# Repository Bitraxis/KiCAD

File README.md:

# My repo for KiCad projects we do at school

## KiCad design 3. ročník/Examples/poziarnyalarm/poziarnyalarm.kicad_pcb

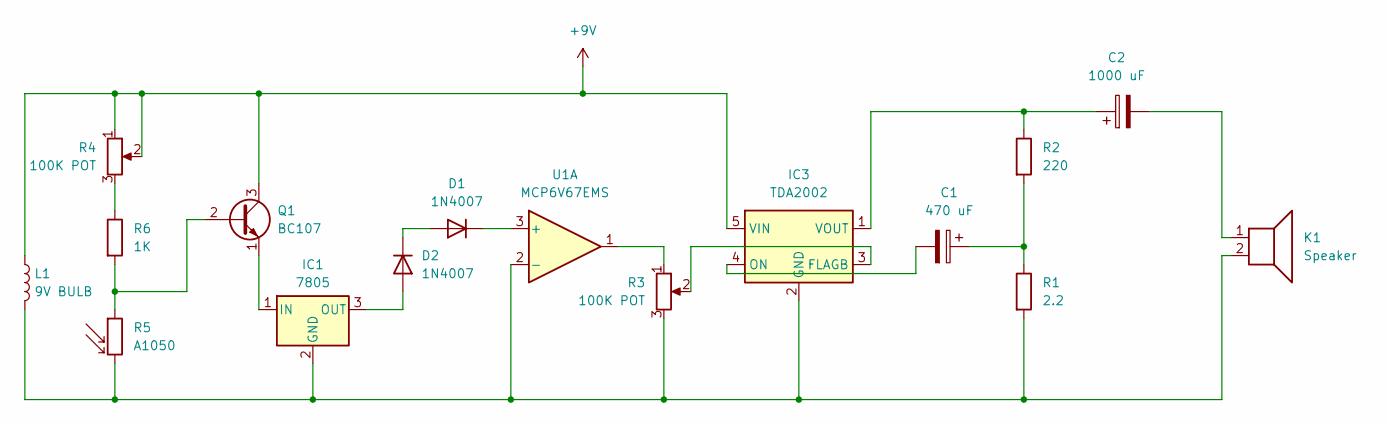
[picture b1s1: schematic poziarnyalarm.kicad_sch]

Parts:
C1: 470 uF; CP_Radial_D5.0mm_P2.50mm
C2: 1000 uF; CP_Radial_D5.0mm_P2.50mm
D1, D2: 1N4007; D_DO-35_SOD27_P10.16mm_Horizontal
IC1: 7805; TO-220F-3_Vertical
IC3: TDA2002; SOT-353_SC-70-5
K1: Speaker; Speaker_CUI_CMR-1206S-67
L1: 9V BULB; L_Radial_D7.0mm_P3.00mm
Q1: BC107; TO-18-3
R1: 2.2; R_Axial_DIN0207_L6.3mm_D2.5mm_P7.62mm_Horizontal
R2: 220; R_Axial_DIN0207_L6.3mm_D2.5mm_P7.62mm_Horizontal
R3, R4: 100K POT; Potentiometer_ACP_CA6-H2,5_Horizontal
R5: A1050; R_LDR_D6.4mm_P3.4mm_Vertical
R6: 1K; R_Axial_DIN0207_L6.3mm_D2.5mm_P7.62mm_Horizontal
U1: MCP6V67EMS; R_Array_BUS_SIP8

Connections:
+9V: IC3.5 (VIN), L1.1, Q1.3 (C), R4.1, R4.2
unnamed: C1.1, R1.1, R2.2
unnamed: C2.2, K1.1
unnamed: D1.2 (A), D2.1 (K)
unnamed: D1.1 (K), U1.3 (+)
unnamed: D2.2 (A), IC1.3 (OUT)
unnamed: IC1.2 (GND), IC3.2 (GND), K1.2, L1.2, R1.2, R3.3, R5.2, U1.2 (-)
unnamed: IC1.1 (IN), Q1.1 (E)
unnamed: IC3.3 (FLAGB), R3.2
unnamed: C1.2, IC3.4 (ON)
unnamed: C2.1, IC3.1 (VOUT), R2.1
unnamed: Q1.2 (B), R5.1, R6.2
unnamed: R3.1, U1.1
unnamed: R4.3, R6.1

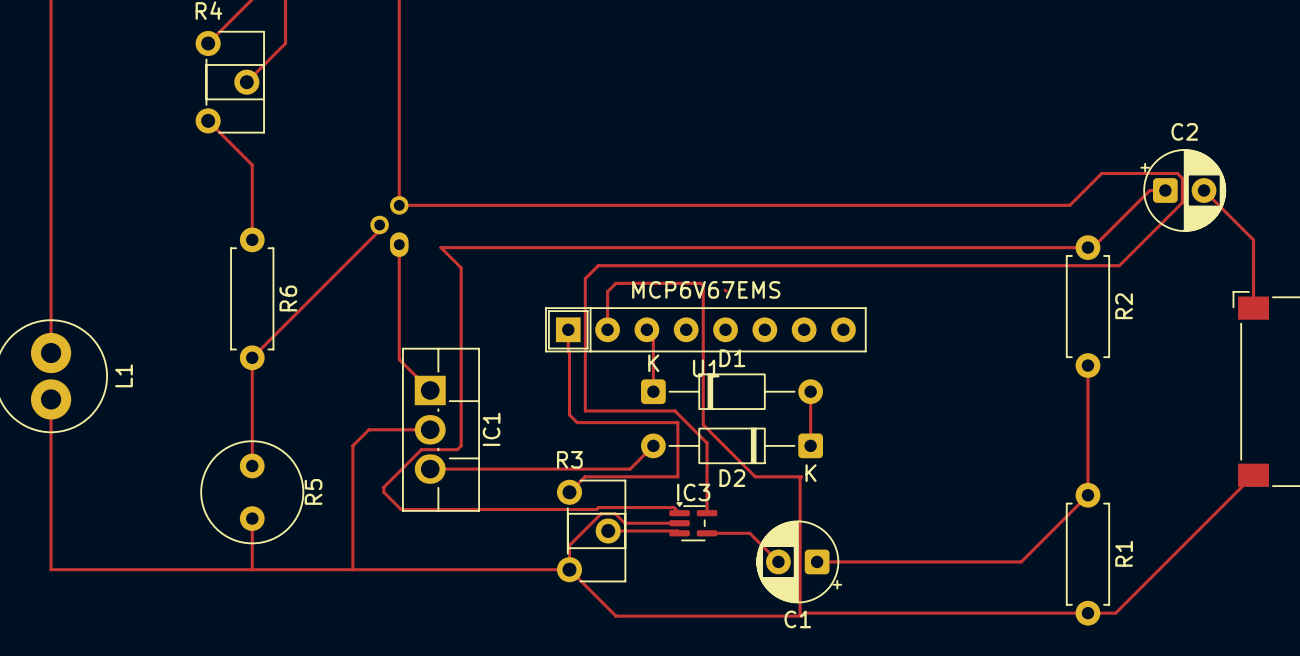
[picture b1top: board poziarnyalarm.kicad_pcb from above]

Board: 2 copper layers, 16 parts (1 on the bottom side), 14 nets.

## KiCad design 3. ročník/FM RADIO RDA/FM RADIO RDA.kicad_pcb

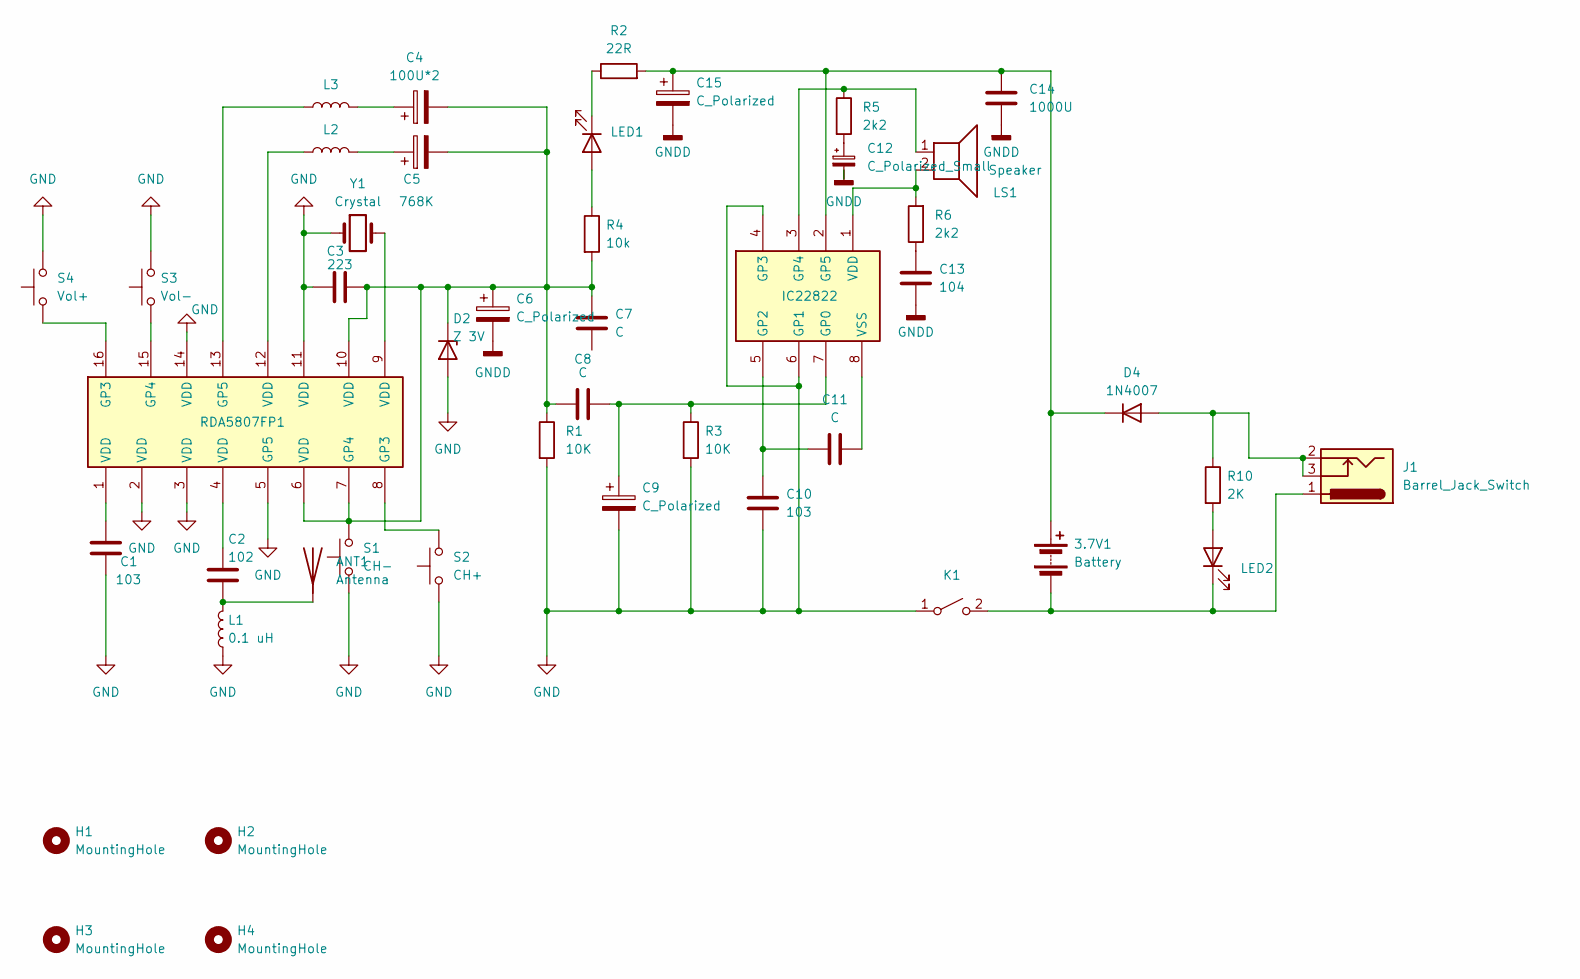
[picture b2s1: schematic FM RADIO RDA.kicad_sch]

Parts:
3.7V1: Battery; BatteryHolder_Keystone_2460_1xAA
ANT1: Antenna; SolderWire-0.1sqmm_1x01_D0.4mm_OD1mm
C1: 103; C_Disc_D3.0mm_W1.6mm_P2.50mm
C2: 102; C_Disc_D3.0mm_W1.6mm_P2.50mm
C3: 223; C_Disc_D3.0mm_W1.6mm_P2.50mm
C4: 100U*2; CP_Radial_D7.5mm_P2.50mm
C5: 768K; CP_Radial_D7.5mm_P2.50mm
C6, C9: C_Polarized; CP_Radial_D4.0mm_P2.00mm
C7, C8: C; C_Disc_D3.0mm_W1.6mm_P2.50mm
C10: 103; C_Rect_L11.0mm_W3.5mm_P10.00mm_MKT
C11: C; C_Rect_L11.0mm_W3.5mm_P10.00mm_MKT
C12: C_Polarized_Small; CP_Radial_D12.5mm_P5.00mm
C13: 104; C_Rect_L11.0mm_W3.5mm_P10.00mm_MKT
C14: 1000U; C_Rect_L11.0mm_W3.5mm_P10.00mm_MKT
C15: C_Polarized; CP_Radial_D7.5mm_P2.50mm
D1: LED1; LED_D3.0mm
D2: Z 3V; D_A-405_P7.62mm_Horizontal
D3: LED2; LED_D3.0mm
D4: 1N4007; D_DO-15_P10.16mm_Horizontal
H1, H2, H3, H4: MountingHole; MountingHole_2.2mm_M2
IC22822: DIP-8_W7.62mm_Socket
J1: Barrel_Jack_Switch; BarrelJack_CUI_PJ-102AH_Horizontal
K1: SW_Slide_SPDT_Angled_CK_OS102011MA1Q
L1: 0.1 uH; L_Axial_L7.0mm_D3.3mm_P10.16mm_Horizontal_Fastron_MICC
L2, L3: L_Axial_L7.0mm_D3.3mm_P10.16mm_Horizontal_Fastron_MICC
LS1: Speaker; SolderWire-0.1sqmm_1x02_P3.6mm_D0.4mm_OD1mm
R1, R3: 10K; R_Axial_DIN0207_L6.3mm_D2.5mm_P7.62mm_Horizontal
R2: 22R; R_Axial_DIN0207_L6.3mm_D2.5mm_P7.62mm_Horizontal
R4: 10k; R_Axial_DIN0207_L6.3mm_D2.5mm_P7.62mm_Horizontal
R5, R6: 2k2; R_Axial_DIN0207_L6.3mm_D2.5mm_P7.62mm_Horizontal
R10: 2K; R_Axial_DIN0207_L6.3mm_D2.5mm_P7.62mm_Horizontal
RDA5807FP1: DIP-16_W8.89mm_SMDSocket_LongPads
S1: CH-; SW_Tactile_SPST_Angled_PTS645Vx58-2LFS
S2: CH+; SW_Tactile_SPST_Angled_PTS645Vx58-2LFS
S3: Vol-; SW_Tactile_SPST_Angled_PTS645Vx58-2LFS
S4: Vol+; SW_Tactile_SPST_Angled_PTS645Vx58-2LFS
Y1: Crystal; Crystal_AT310_D3.0mm_L10.0mm_Vertical

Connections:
GND: C1.2, C3.1, C9.2, C10.2, D2.2 (A), IC22822.4 (GP3), IC22822.6 (GP1), K1.1 (A), L1.1, R1.2, R3.2, RDA5807FP1.2 (VDD), RDA5807FP1.3 (VDD), RDA5807FP1.5 (GP5), RDA5807FP1.11 (VDD), RDA5807FP1.14 (VDD), S1.1, S2.1, S3.2, S4.2, Y1.1
GNDD: C6.2, C12.2, C13.2, C14.2, C15.2
unnamed: 3.7V1.1 (+), C14.1, C15.1, D4.1 (K), IC22822.2 (GP5), R2.2
unnamed: 3.7V1.2 (-), D3.1 (K), J1.1, K1.2 (B)
unnamed: ANT1.1 (A), C2.1, L1.2
unnamed: C1.1, RDA5807FP1.1 (VDD)
unnamed: C2.2, RDA5807FP1.4 (VDD)
unnamed: C4.1, L3.2
unnamed: C5.1, L2.2
unnamed: C12.1, R5.2
unnamed: C13.1, R6.1
unnamed: D1.2 (A), R4.1
unnamed: D1.1 (K), R2.1
unnamed: C3.2, C4.2, C5.2, C6.1, C7.1, C8.1, D2.1 (K), R1.1, R4.2, RDA5807FP1.6 (VDD), RDA5807FP1.7 (GP4), RDA5807FP1.10 (VDD), S1.2
unnamed: D3.2 (A), R10.2
unnamed: D4.2 (A), J1.2, J1.3, R10.1
unnamed: C8.2, C9.1, IC22822.7 (GP0), R3.1
unnamed: C10.1, C11.1, IC22822.5 (GP2)
unnamed: IC22822.3 (GP4), LS1.1, R5.1
unnamed: IC22822.1 (VDD), LS1.2, R6.2
unnamed: C11.2, IC22822.8 (VSS)
unnamed: L2.1, RDA5807FP1.12 (VDD)
unnamed: L3.1, RDA5807FP1.13 (GP5)
unnamed: RDA5807FP1.8 (GP3), S2.2
unnamed: RDA5807FP1.16 (GP3), S4.1
unnamed: RDA5807FP1.15 (GP4), S3.1
unnamed: RDA5807FP1.9 (VDD), Y1.2

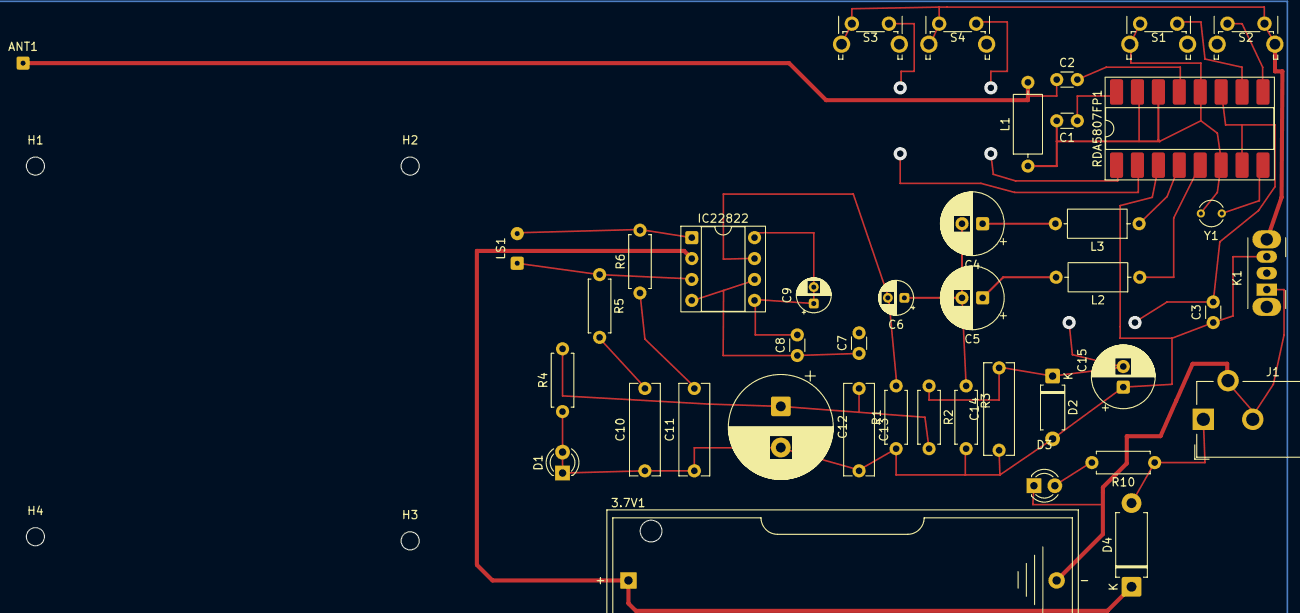
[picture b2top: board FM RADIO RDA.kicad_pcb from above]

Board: 2 copper layers, 45 parts (0 on the bottom side), 27 nets.

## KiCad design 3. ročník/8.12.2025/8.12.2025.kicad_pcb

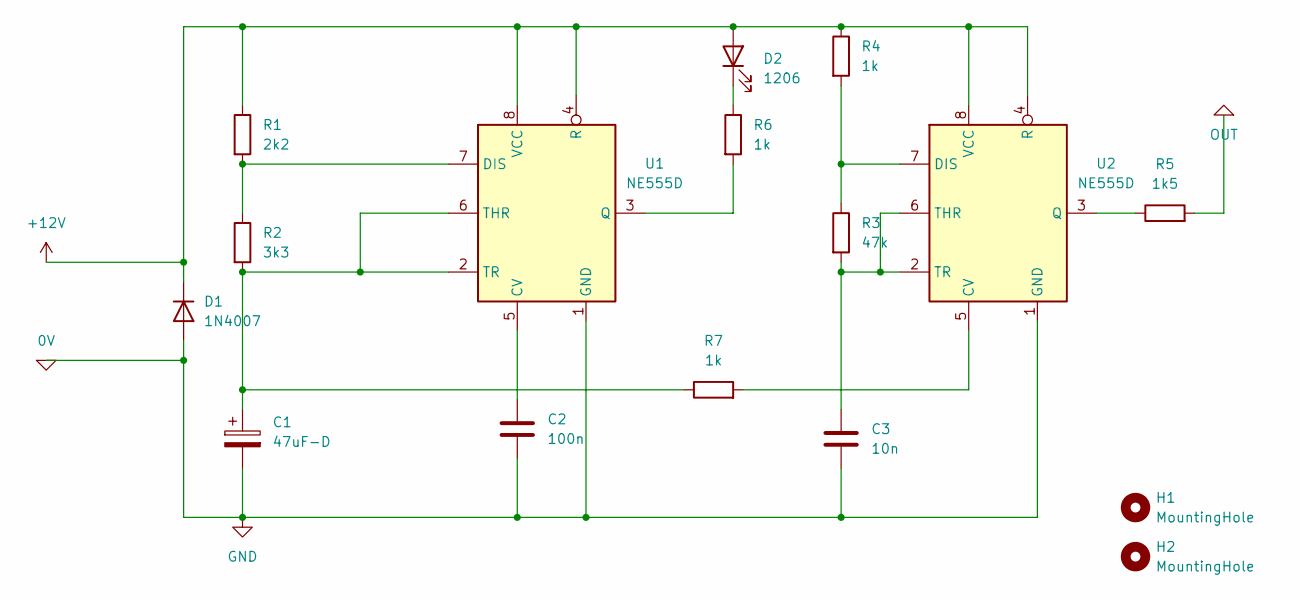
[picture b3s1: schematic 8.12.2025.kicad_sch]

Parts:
C1: 47uF-D; C_0402_1005Metric
C2: 100n; C_0402_1005Metric
C3: 10n; C_0402_1005Metric
D1: 1N4007; D_0402_1005Metric
D2: 1206; LED_0402_1005Metric
H1, H2: MountingHole; MountingHole_2.2mm_M2
R1: 2k2; R_0402_1005Metric
R2: 3k3; R_0402_1005Metric
R3: 47k; R_0402_1005Metric
R4, R6, R7: 1k; R_0402_1005Metric
R5: 1k5; R_0402_1005Metric
U1, U2: NE555D; SOIC-8_3.9x4.9mm_P1.27mm

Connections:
0V: C1.2, C2.2, C3.2, D1.2 (A), U1.1 (GND), U2.1 (GND)
+12V: D1.1 (K), D2.2 (A), R1.1, R4.1, U1.4 (R), U1.8 (VCC), U2.4 (R), U2.8 (VCC)
unnamed: D2.1 (K), R6.1
unnamed: C2.1, U1.5 (CV)
unnamed: R1.2, R2.1, U1.7 (DIS)
unnamed: R6.2, U1.3 (Q)
unnamed: C1.1, R2.2, R7.1, U1.2 (TR), U1.6 (THR)
unnamed: R7.2, U2.5 (CV)
unnamed: R3.1, R4.2, U2.7 (DIS)
unnamed: R5.1, U2.3 (Q)
unnamed: C3.1, R3.2, U2.2 (TR), U2.6 (THR)
OUT: R5.2

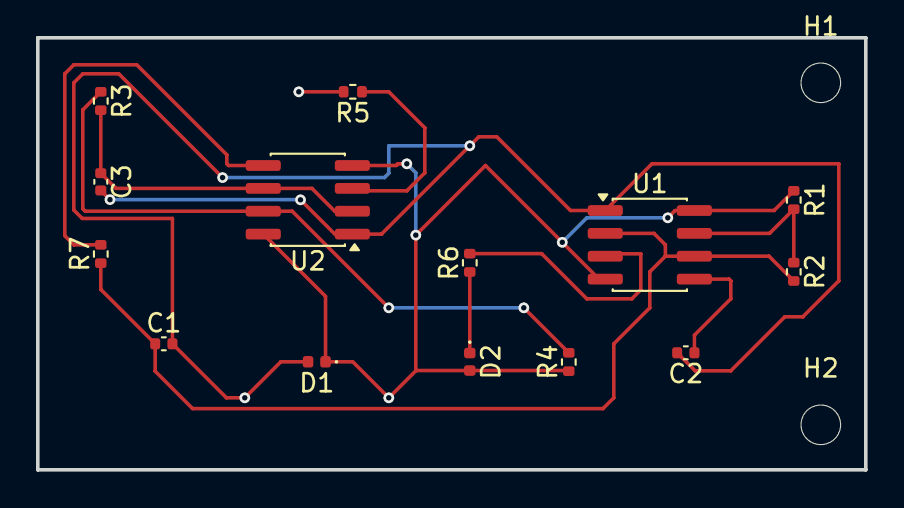
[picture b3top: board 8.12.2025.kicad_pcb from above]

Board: 2 copper layers, 46.0 x 24.0 mm, 16 parts (0 on the bottom side), 11 nets.

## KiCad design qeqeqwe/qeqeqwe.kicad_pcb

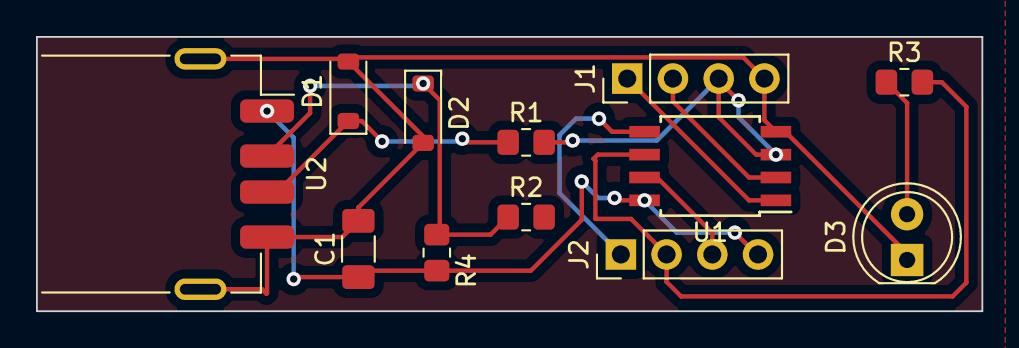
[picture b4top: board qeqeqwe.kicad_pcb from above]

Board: 2 copper layers, 52.5 x 15.2 mm, 12 parts (0 on the bottom side), 11 nets.

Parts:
C1: 100nF; C_1206_3216Metric_Pad1.33x1.80mm_HandSolder
D1, D2: 3V6; D_SOD-123
D3: LED; LED_D5.0mm
J1, J2: Conn_01x04; PinHeader_1x04_P2.54mm_Vertical
R1, R2, R3, R4: 68Ω; R_0805_2012Metric_Pad1.20x1.40mm_HandSolder
U1: ATtiny85-20S; SOIC-8W_5.3x5.3mm_P1.27mm
U2: USB_A; USB_A_Receptacle_GCT_USB1046

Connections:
+5V: C1.1, J2.4, R4.2, U1.8 (VCC), U2.1 (VBUS)
GND: C1.2, D1.2 (A), D2.2 (A), D3.1 (K), J1.4, U1.4 (GND), U2.4 (GND), U2.5 (Shield)
unnamed: D1.1 (K), R1.1, U2.3 (D+)
unnamed: D2.1 (K), R2.1, R4.1, U2.2 (D-)
unnamed: D3.2 (A), R3.1
unnamed: J1.1, U1.1 (~RESET/PB5)
unnamed: J1.2, R2.2, U1.2 (XTAL1/PB3)
unnamed: J1.3, R1.2, U1.3 (XTAL2/PB4)
unnamed: J2.1, U1.5 (AREF/PB0)
unnamed: J2.2, R3.2, U1.6 (PB1)
unnamed: J2.3, U1.7 (PB2)

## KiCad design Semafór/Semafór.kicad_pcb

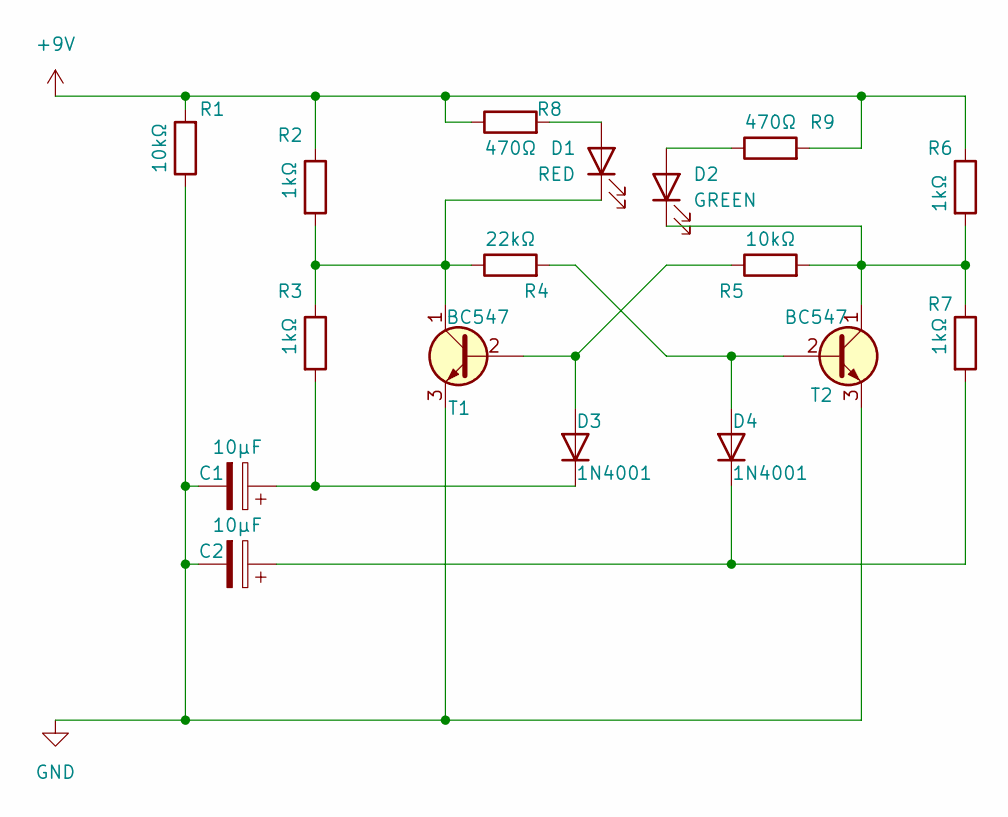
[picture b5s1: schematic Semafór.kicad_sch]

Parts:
C1, C2: 10µF; CP_Radial_D5.0mm_P2.50mm
D1: RED; LED_D5.0mm
D2: GREEN; LED_D5.0mm
D3, D4: 1N4001; D_DO-41_SOD81_P10.16mm_Horizontal
R1, R5: 10kΩ; R_Axial_DIN0207_L6.3mm_D2.5mm_P10.16mm_Horizontal
R2, R3, R6, R7: 1kΩ; R_Axial_DIN0207_L6.3mm_D2.5mm_P10.16mm_Horizontal
R4: 22kΩ; R_Axial_DIN0207_L6.3mm_D2.5mm_P10.16mm_Horizontal
R8, R9: 470Ω; R_Axial_DIN0207_L6.3mm_D2.5mm_P10.16mm_Horizontal
T1, T2: BC547; TO-92_Inline_Wide

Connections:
+9V: R1.2, R2.1, R6.1, R8.1, R9.2
GND: C1.2, C2.2, R1.1, T1.3 (E), T2.3 (E)
unnamed: D1.2 (A), R8.2
unnamed: D1.1 (K), R2.2, R3.1, R4.1, T1.1 (C)
unnamed: D2.2 (A), R9.1
unnamed: D2.1 (K), R5.2, R6.2, R7.1, T2.1 (C)
unnamed: D3.2 (A), R5.1, T1.2 (B)
unnamed: C1.1, D3.1 (K), R3.2
unnamed: D4.2 (A), R4.2, T2.2 (B)
unnamed: C2.1, D4.1 (K), R7.2

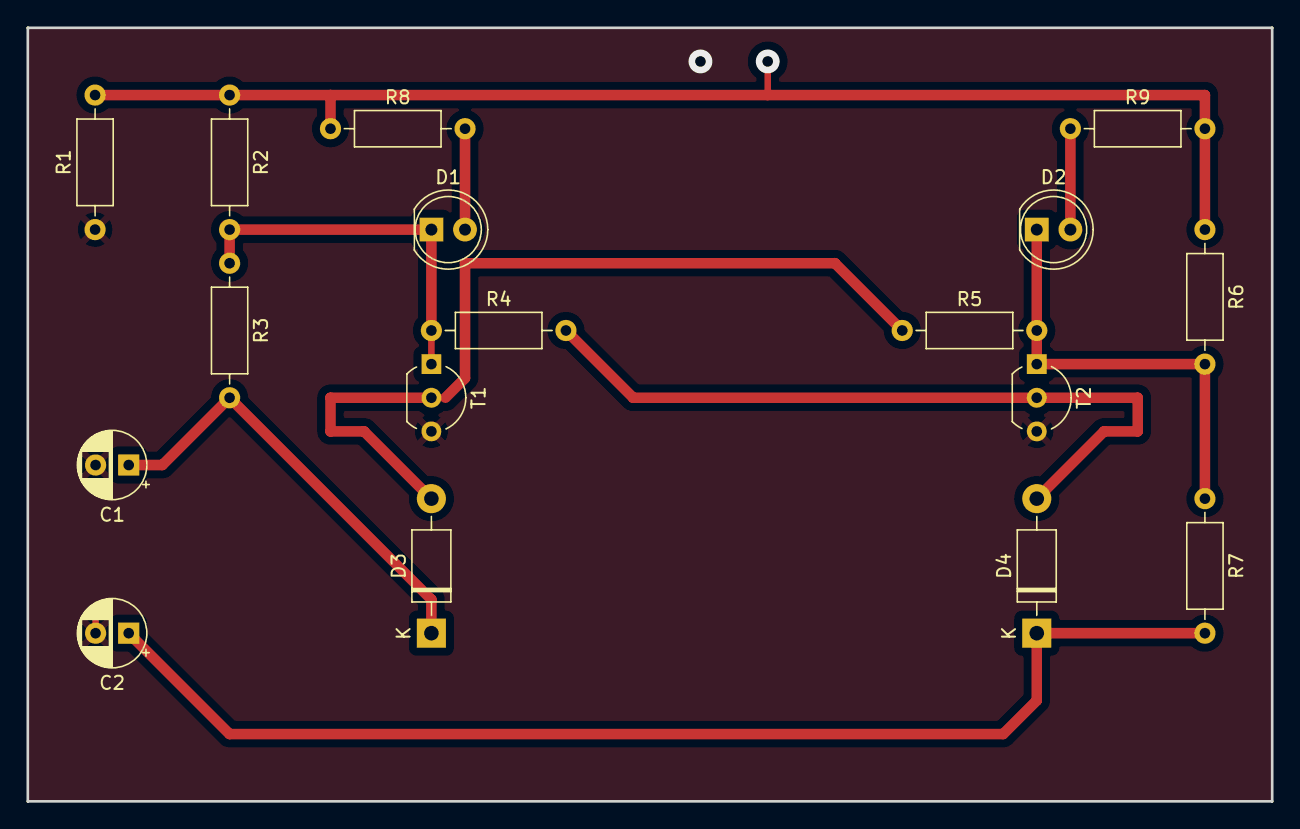
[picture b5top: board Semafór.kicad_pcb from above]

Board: 2 copper layers, 94.0 x 58.4 mm, 17 parts (0 on the bottom side), 10 nets.

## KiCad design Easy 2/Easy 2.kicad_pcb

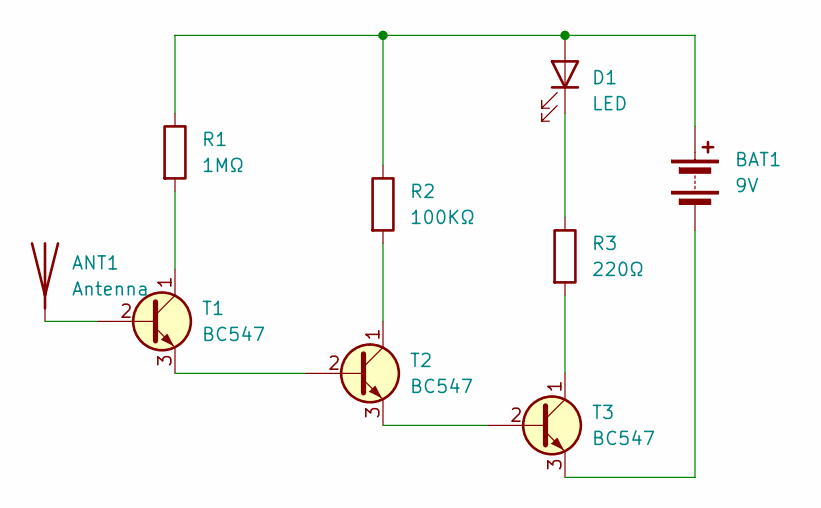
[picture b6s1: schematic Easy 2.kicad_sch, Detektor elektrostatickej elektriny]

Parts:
ANT1: Antenna; Astrocast_AST50127-00
BAT1: 9V; BatteryHolder_Keystone_2462_2xAA
D1: LED; LED_D5.0mm
R1: 1MΩ; R_Axial_DIN0207_L6.3mm_D2.5mm_P7.62mm_Horizontal
R2: 100KΩ; R_Axial_DIN0207_L6.3mm_D2.5mm_P7.62mm_Horizontal
R3: 220Ω; R_Axial_DIN0207_L6.3mm_D2.5mm_P7.62mm_Horizontal
T1, T2, T3: BC547; TO-92_Inline_Wide

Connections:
unnamed: ANT1.1 (A), T1.2 (B)
unnamed: BAT1.1 (+), D1.2 (A), R1.1, R2.1
unnamed: BAT1.2 (-), T3.3 (E)
unnamed: D1.1 (K), R3.1
unnamed: R1.2, T1.1 (C)
unnamed: T1.3 (E), T2.2 (B)
unnamed: R2.2, T2.1 (C)
unnamed: T2.3 (E), T3.2 (B)
unnamed: R3.2, T3.1 (C)

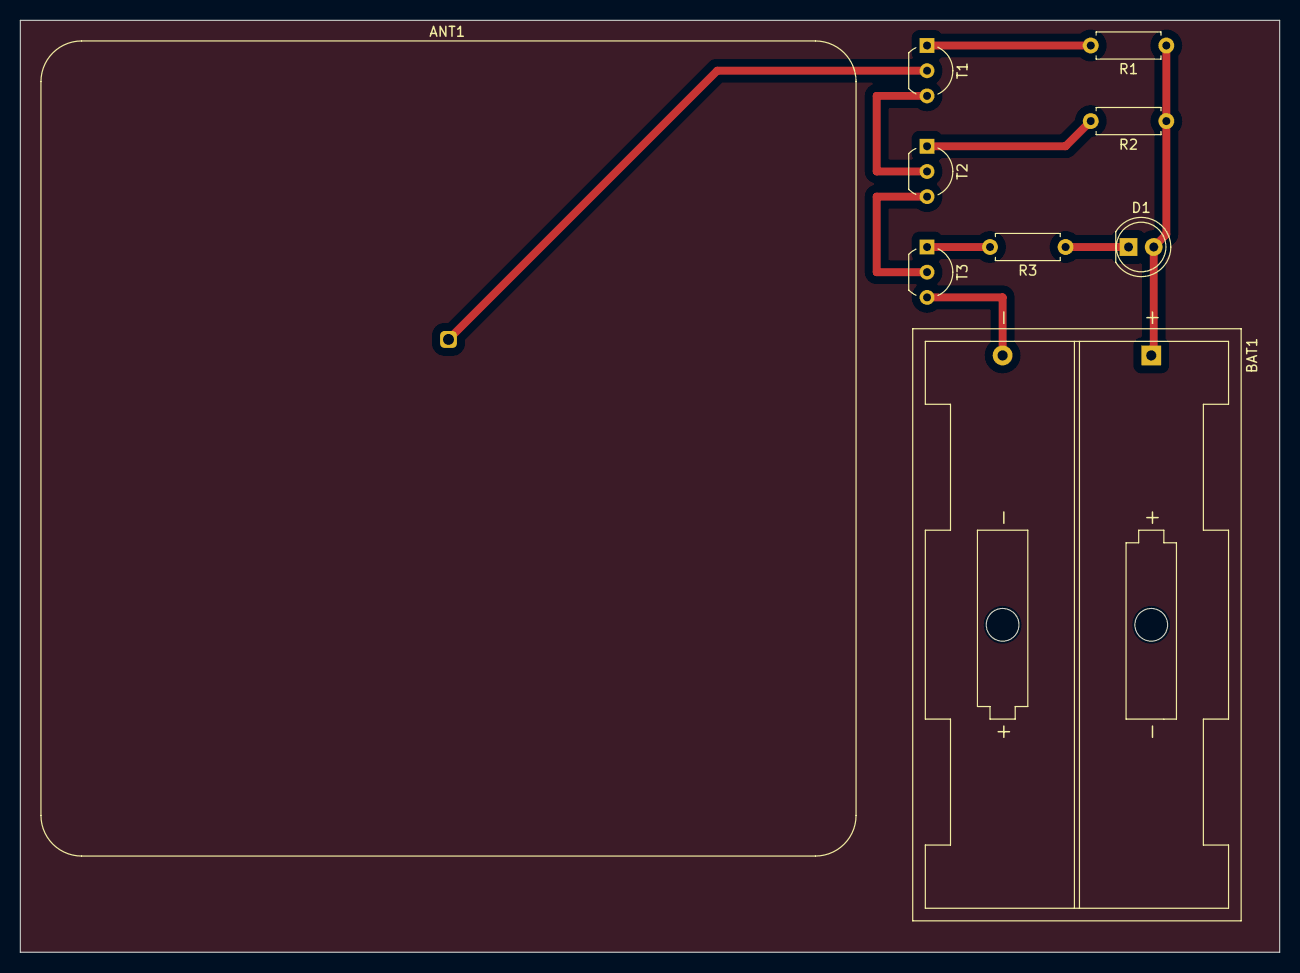
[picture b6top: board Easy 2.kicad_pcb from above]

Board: 2 copper layers, 127.0 x 94.0 mm, 9 parts (0 on the bottom side), 9 nets.

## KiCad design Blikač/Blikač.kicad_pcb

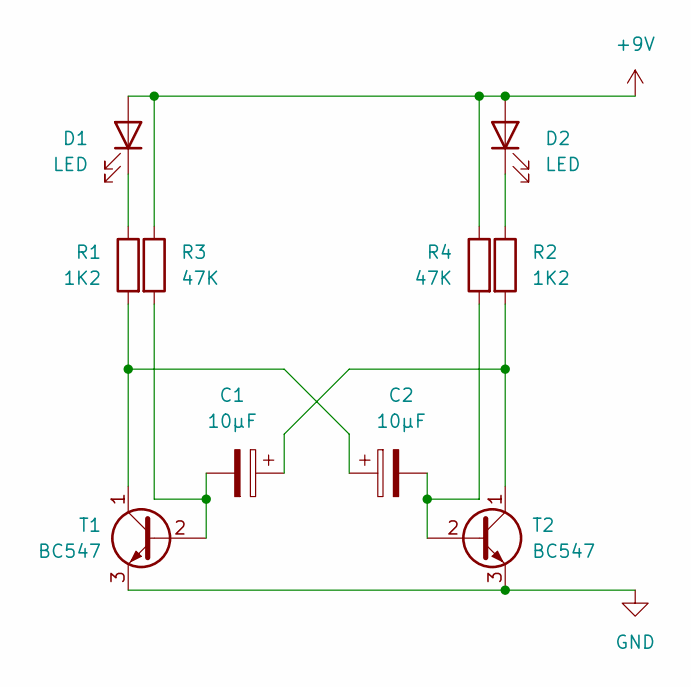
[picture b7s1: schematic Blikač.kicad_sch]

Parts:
C1, C2: 10µF; CP_Radial_D5.0mm_P2.50mm
D1, D2: LED; LED_D5.0mm
R1, R2: 1K2; R_Axial_DIN0207_L6.3mm_D2.5mm_P10.16mm_Horizontal
R3, R4: 47K; R_Axial_DIN0207_L6.3mm_D2.5mm_P10.16mm_Horizontal
T1, T2: BC547; TO-92_Inline_Wide

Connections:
+9V: D1.2 (A), D2.2 (A), R3.1, R4.1
GND: T1.3 (E), T2.3 (E)
unnamed: D1.1 (K), R1.1
unnamed: D2.1 (K), R2.1
unnamed: C1.2, R3.2, T1.2 (B)
unnamed: C2.1, R1.2, T1.1 (C)
unnamed: C2.2, R4.2, T2.2 (B)
unnamed: C1.1, R2.2, T2.1 (C)

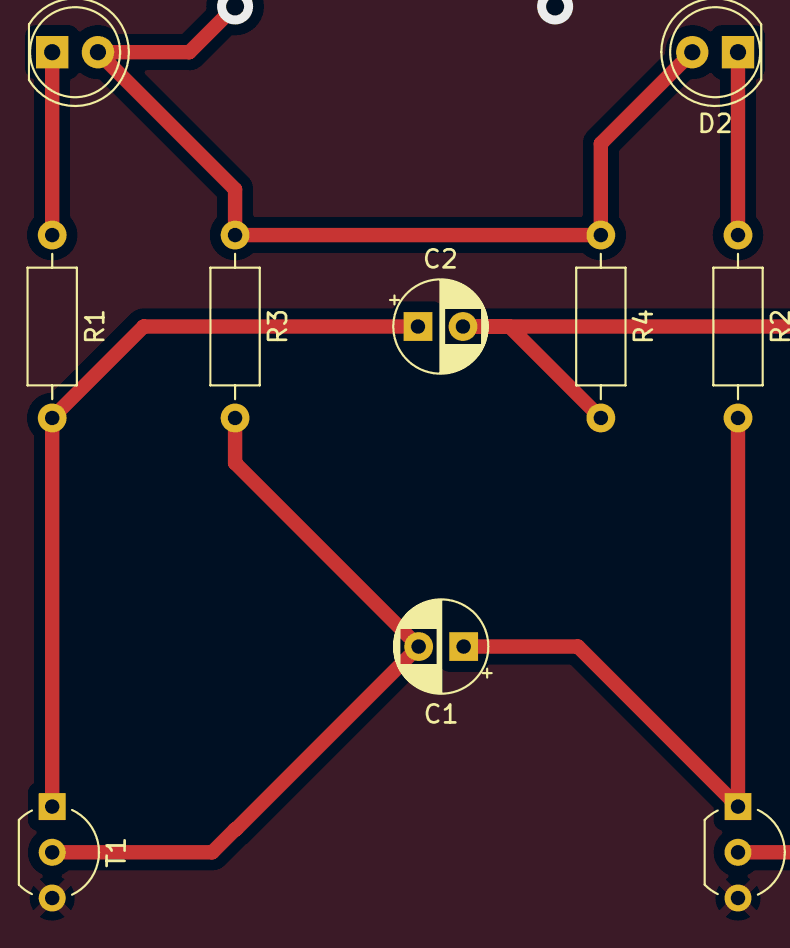
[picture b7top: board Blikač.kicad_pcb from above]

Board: 2 copper layers, 10 parts (0 on the bottom side), 8 nets.

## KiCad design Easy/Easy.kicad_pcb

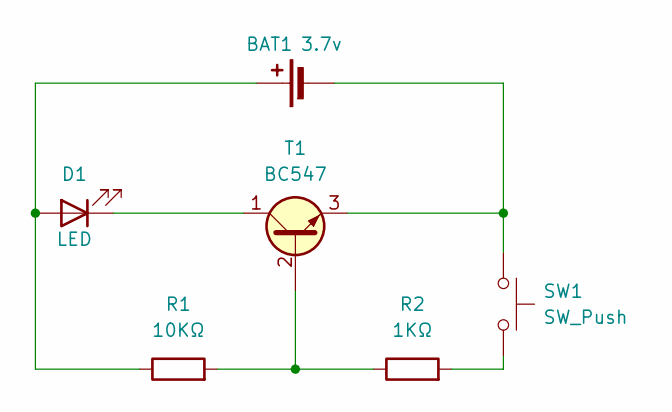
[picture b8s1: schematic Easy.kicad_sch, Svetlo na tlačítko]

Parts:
BAT1: 3.7v; BatteryHolder_Keystone_103_1x20mm
D1: LED; LED_D5.0mm
R1: 10KΩ; R_Axial_DIN0207_L6.3mm_D2.5mm_P7.62mm_Horizontal
R2: 1KΩ; R_Axial_DIN0207_L6.3mm_D2.5mm_P7.62mm_Horizontal
SW1: SW_Push; SW_PUSH_6mm_H8.5mm
T1: BC547; TO-92_Inline_Wide

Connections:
unnamed: BAT1.1 (+), D1.2 (A), R1.1
unnamed: BAT1.2 (-), SW1.1, T1.3 (E)
unnamed: D1.1 (K), T1.1 (C)
unnamed: R2.2, SW1.2
unnamed: R1.2, R2.1, T1.2 (B)

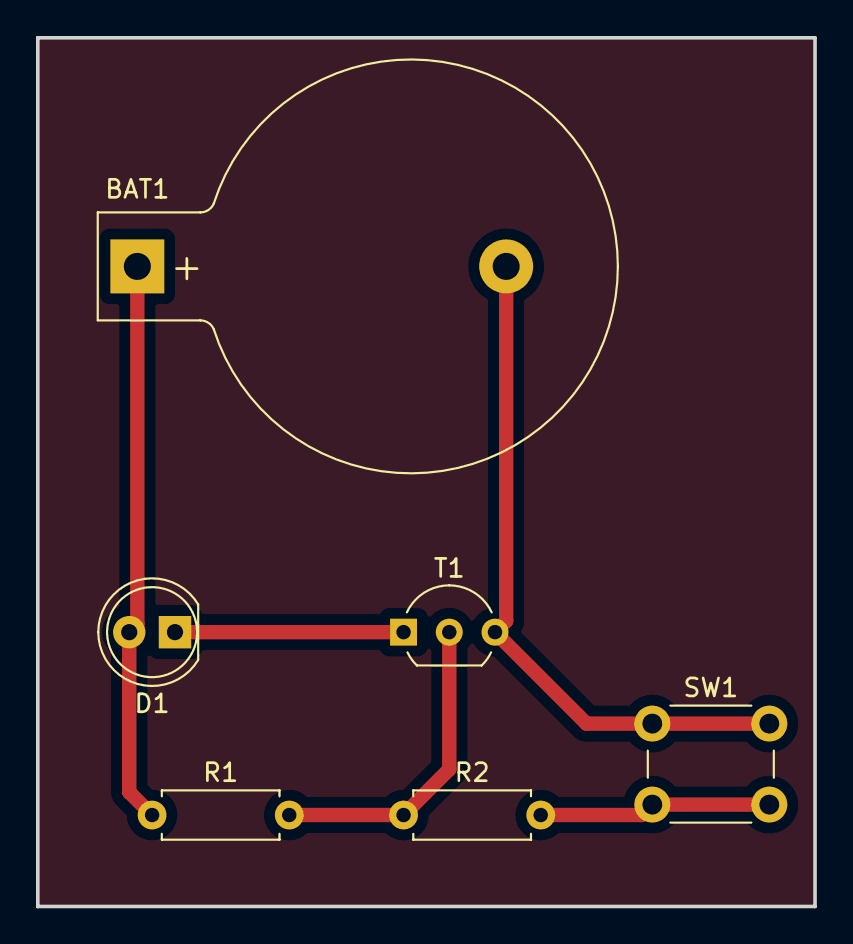
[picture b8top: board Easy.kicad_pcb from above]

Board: 2 copper layers, 43.2 x 48.3 mm, 6 parts (0 on the bottom side), 5 nets.

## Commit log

2025-05-14 Make the repo
2025-05-14 Test
2025-05-16 novy projekt
2025-05-30 dgdgegergregre
2025-06-18 bkbbj
2025-09-30 WRWE
2025-10-20 adasd
2025-10-20 asdasdasd
2025-10-20 rwrwerwer
2025-10-20 were
2025-10-20 weqwe
2025-10-20 asdasdad
2025-10-23 Hello
2025-10-27 jasdfds
2025-11-03 ajsd
2025-11-10 qwdq
2025-12-02 werwer
2025-12-02 HAHA
2025-12-08 Jasads
2025-12-08 asdad
2026-01-19 hjhj
2026-02-02 hlasic
